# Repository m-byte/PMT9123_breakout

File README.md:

PMT9123 Breakout
================

License Information
-------------------
This design is [OSHW](http://www.oshwa.org/definition/) and public domain but you buy me a beer if you use this and we meet someday ([Beerware license](http://en.wikipedia.org/wiki/Beerware)).

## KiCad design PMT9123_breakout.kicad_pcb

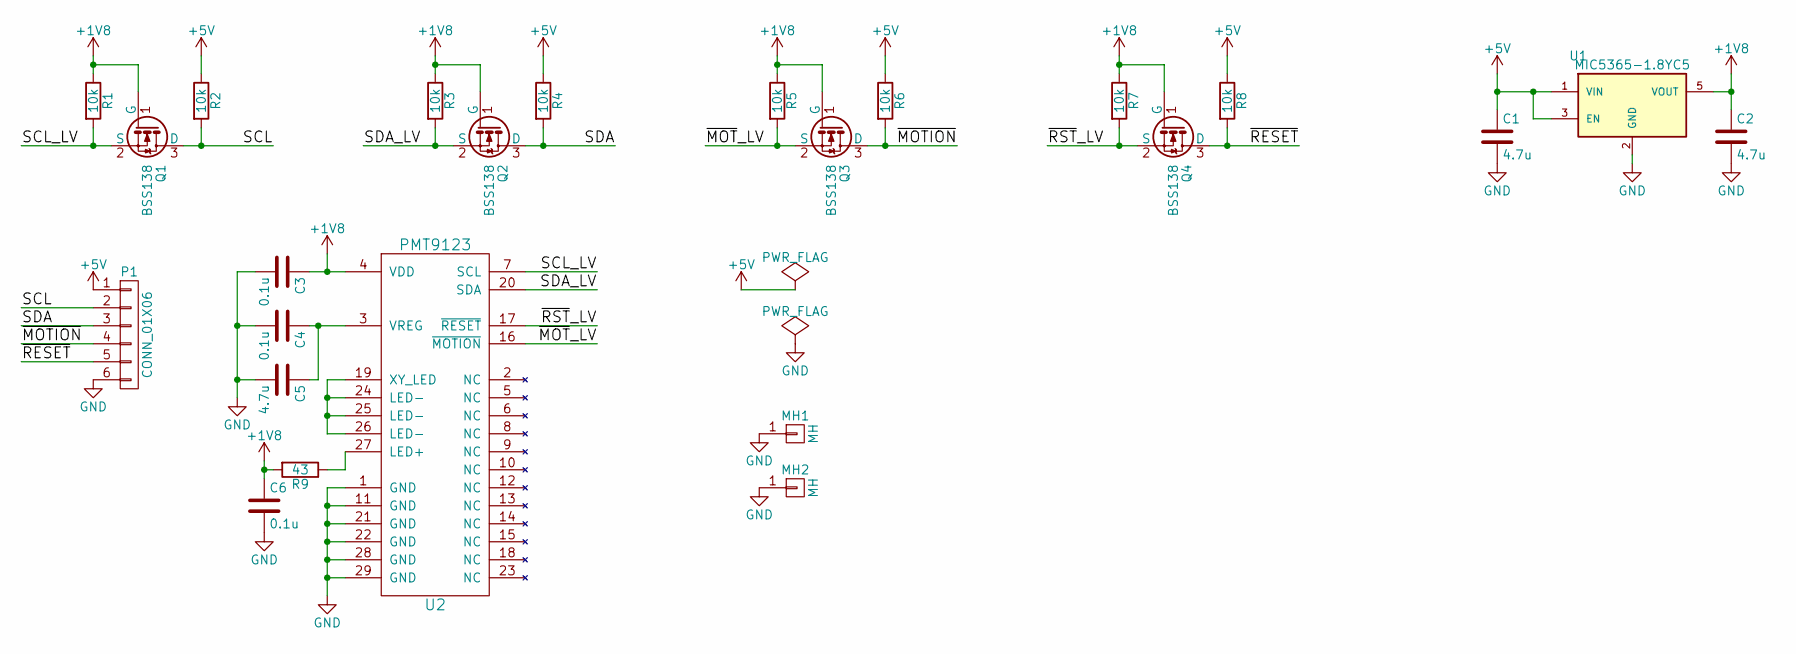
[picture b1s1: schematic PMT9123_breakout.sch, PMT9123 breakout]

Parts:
C1, C2, C5: 4.7u; C_0805
C3, C4, C6: 0.1u; C_0805
MH1, MH2: MH; MountingHole_2.2mm_M2_Pad_Via
P1: CONN_01X06; Pin_Header_Straight_1x06
Q1, Q2, Q3, Q4: BSS138; SOT-23
R1, R2, R3, R4, R5, R6, R7, R8: 10k; R_0805
R9: 43; R_0805
U1: MIC5365-1.8YC5; SC-70-5
U2: PMT9123

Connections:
+1V8: C2.1, C3.1, C6.1, Q1.1 (G), Q2.1 (G), Q3.1 (G), Q4.1 (G), R1.1, R3.1, R5.1, R7.1, R9.2, U1.5 (VOUT), U2.4 (VDD)
+5V: C1.1, P1.1, R2.1, R4.1, R6.1, R8.1, U1.1 (VIN), U1.3 (EN)
/SCL: P1.2, Q1.3 (D), R2.2
/SCL_LV: Q1.2 (S), R1.2, U2.7 (SCL)
/SDA: P1.3, Q2.3 (D), R4.2
/SDA_LV: Q2.2 (S), R3.2, U2.20 (SDA)
/~MOTION: P1.4, Q3.3 (D), R6.2
/~MOT~_LV: Q3.2 (S), R5.2, U2.16 (~MOTION)
/~RESET: P1.5, Q4.3 (D), R8.2
/~RST~_LV: Q4.2 (S), R7.2, U2.17 (~RESET)
GND: C1.2, C2.2, C3.2, C4.2, C5.2, C6.2, MH1.1, MH2.1, P1.6, U1.2 (GND), U2.1 (GND), U2.11 (GND), U2.21 (GND), U2.22 (GND), U2.28 (GND), U2.29 (GND)
unnamed: C4.1, C5.1, U2.3 (VREG)
unnamed: R9.1, U2.27 (LED+)
unnamed: U2.19 (XY_LED), U2.24 (LED-), U2.25 (LED-), U2.26 (LED-)

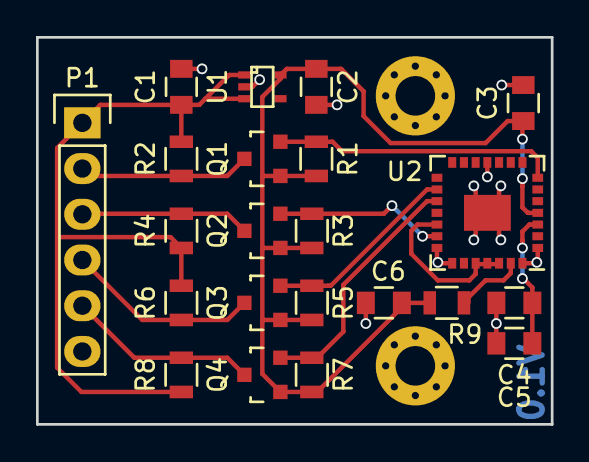
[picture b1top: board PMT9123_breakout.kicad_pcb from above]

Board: 2 copper layers, 28.6 x 21.5 mm, 24 parts (0 on the bottom side), 14 nets.

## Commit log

2016-11-22 init
2016-11-22 added missing footprints
2016-11-22 started pcb
2016-11-22 PCB done
